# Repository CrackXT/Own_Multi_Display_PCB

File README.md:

# Own_Multi_Display_PCB

PCB files for Multi Display Board

# Description

This board serves as a development platform for finished devices with different display sizes.

- MiP 2,7" https://www.adafruit.com/product/4694
- TFT IPS 1,9" https://www.adafruit.com/product/5394
- TFT IPS 1,69" https://www.adafruit.com/product/5206
- TFT IPS 1,47" https://www.adafruit.com/product/5393

With a programmable status LED (RGB, SK6812-E) and an ambient light sensor (analogue, ALS-PT19) to regulate the brightness of TFT screens.

The screen, LED and ambient light sensor can be controlled via the existing Featherformat socket and the MCU used in it.

The board can be produced here (AISLER) with the files (.brd and .sch) or by any other PCB manufacturer. -> https://aisler.net/

# Serie

- .dev

# Layout

Top<br>

Bottom<br>

Routing/Dimensions(inch)<br>

Schematic<br>
Schematic as .pdf at the top of the page.

# License

Open hardware, use it, mod it, whatever you want, feel free...

# Thanks!

Own design and layout.

# Version - Build

v1.0 - 05.11.2022

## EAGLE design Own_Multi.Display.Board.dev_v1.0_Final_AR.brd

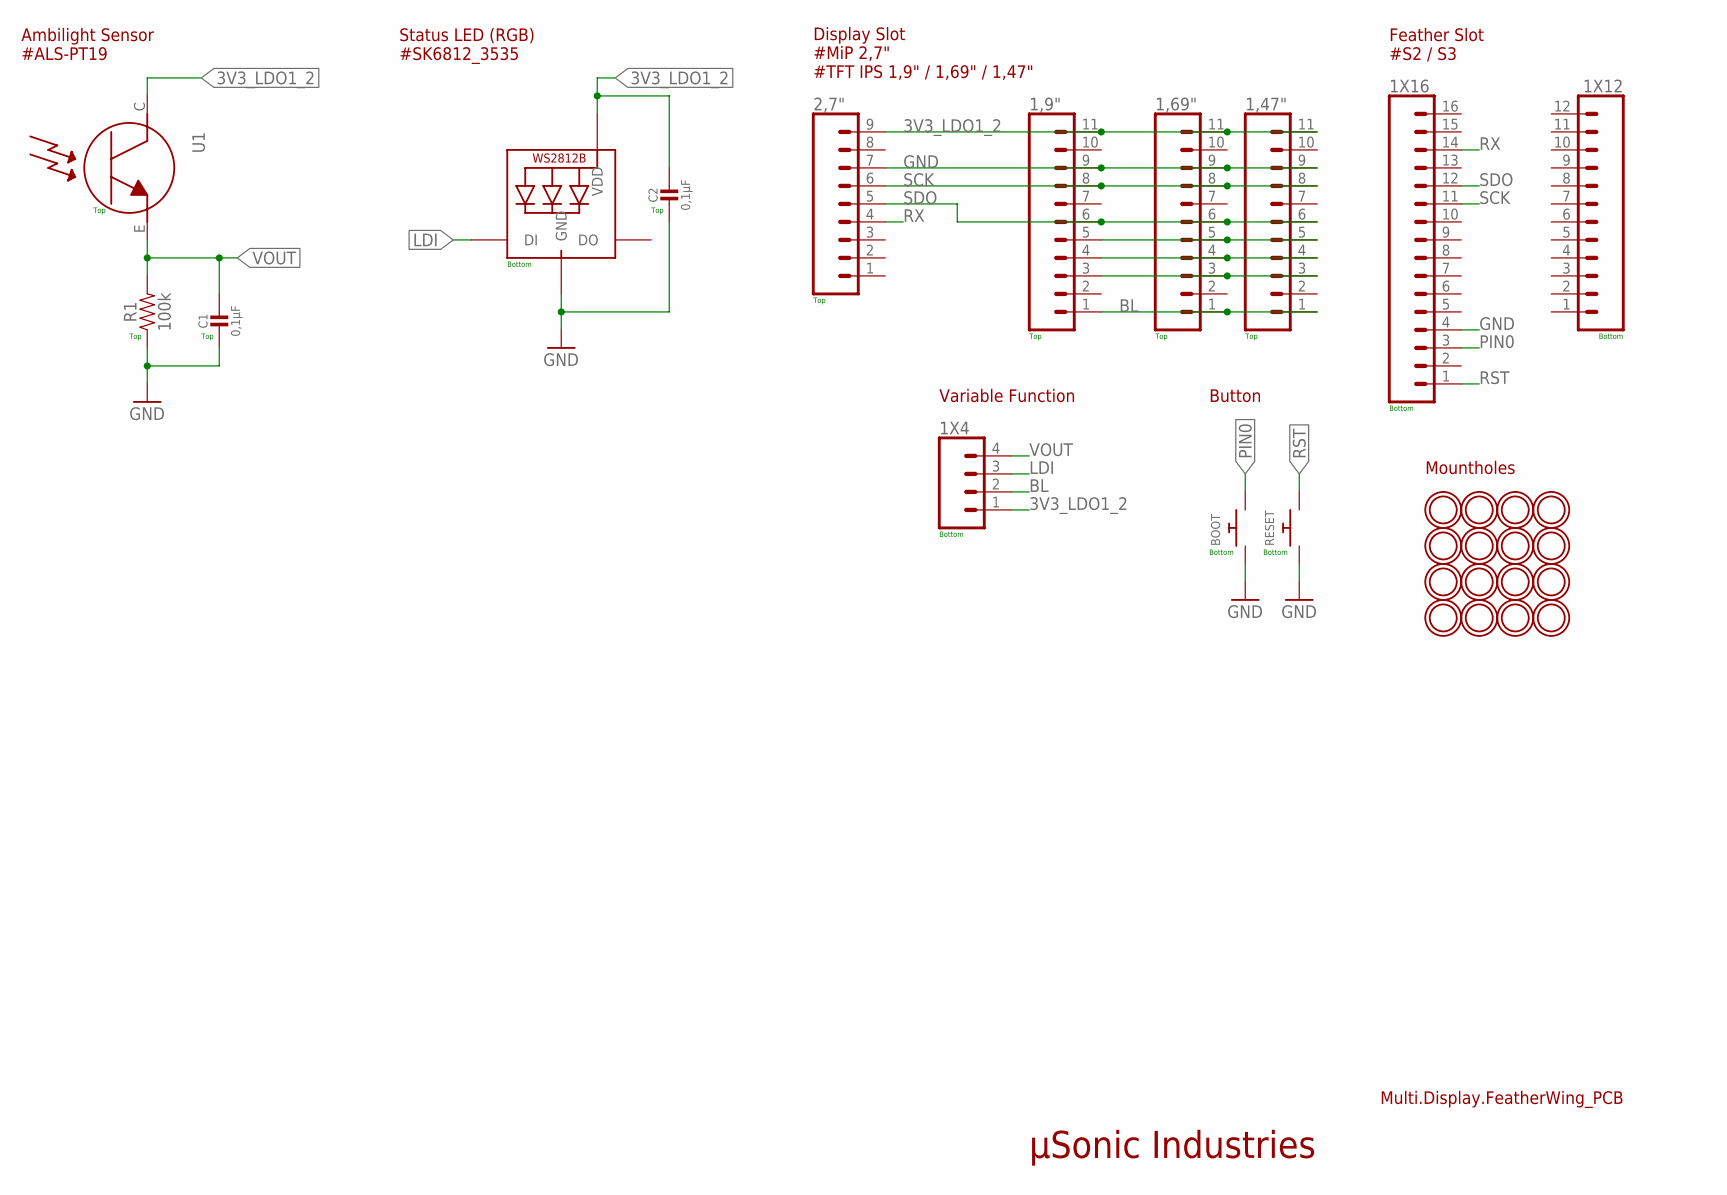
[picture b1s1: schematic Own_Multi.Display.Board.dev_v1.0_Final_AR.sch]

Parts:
1,9", 1,47", 1,69": CONN_111X11_NO_SILK; 1X11_NO_SILK
1X4: CONN_041X04_NO_SILK; 1X04_NO_SILK
1X12: CONN_12NO_SILK; 1X12_NO_SILK
1X16: CONN_161X16_NO_SILK; 1X16_NO_SILK
2,7": CONN_09NO_SILK; 1X09_NO_SILK
BOOT: SWITCH_PUSHBUTTONSF_OWN; OWN_TACT_PANA-EVQ
C1, C2: 0,1µF; MICROBUILDER_0805_10MGAP
LED1: MICROBUILDER_WS2812B_SK6812E; MICROBUILDER_NEO3535_REVERSE
R1: 100k; 0805
RESET: SWITCH_PUSHBUTTONSF_OWN; OWN_TACT_PANA-EVQ
U1: MICROBUILDER_LIGHT_ALS-PT19-315C; MICROBUILDER_ALS-PT19-315C
U$5, U$8, U$16, U$18, U$19, U$23, U$24, U$25, U$26, U$27, U$28, U$29, U$30, U$31, U$32, U$33: MOUNTINGHOLE2.5; MOUNTINGHOLE_2.5_PLATED

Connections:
3V3_LDO1_2: 1,9".11, 1,47".11, 1,69".11, 1X4.1, 2,7".9, C2.1, LED1.1-VDD (VDD), U1.C
BL: 1,9".1, 1,47".1, 1,69".1, 1X4.2
GND: 1,9".9, 1,47".9, 1,69".9, 1X16.4, 2,7".7, BOOT.P$1, C1.2, C2.2, LED1.3-GND (GND), R1.1, RESET.P$1
LDI: 1X4.3, LED1.4-DIN (DI)
unnamed: 1,9".5, 1,47".5, 1,69".5
unnamed: 1,9".4, 1,47".4, 1,69".4
unnamed: 1,9".3, 1,47".3, 1,69".3
PIN0: 1X16.3, BOOT.P$2
RST: 1X16.1, RESET.P$2
RX: 1X16.14, 2,7".4
SCK: 1,9".8, 1,47".8, 1,69".8, 1X16.11, 2,7".6
SDO: 1,9".6, 1,47".6, 1,69".6, 1X16.12, 2,7".5
VOUT: 1X4.4, C1.1, R1.2, U1.E

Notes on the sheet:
µSonic Industries
Multi.Display.FeatherWing_PCB
Ambilight Sensor #ALS-PT19
Mountholes
Top
Bottom
Status LED (RGB) #SK6812_3535
Display Slot #MiP 2,7" #TFT IPS 1,9" / 1,69" / 1,47"
Variable Function
Button
Feather Slot #S2 / S3

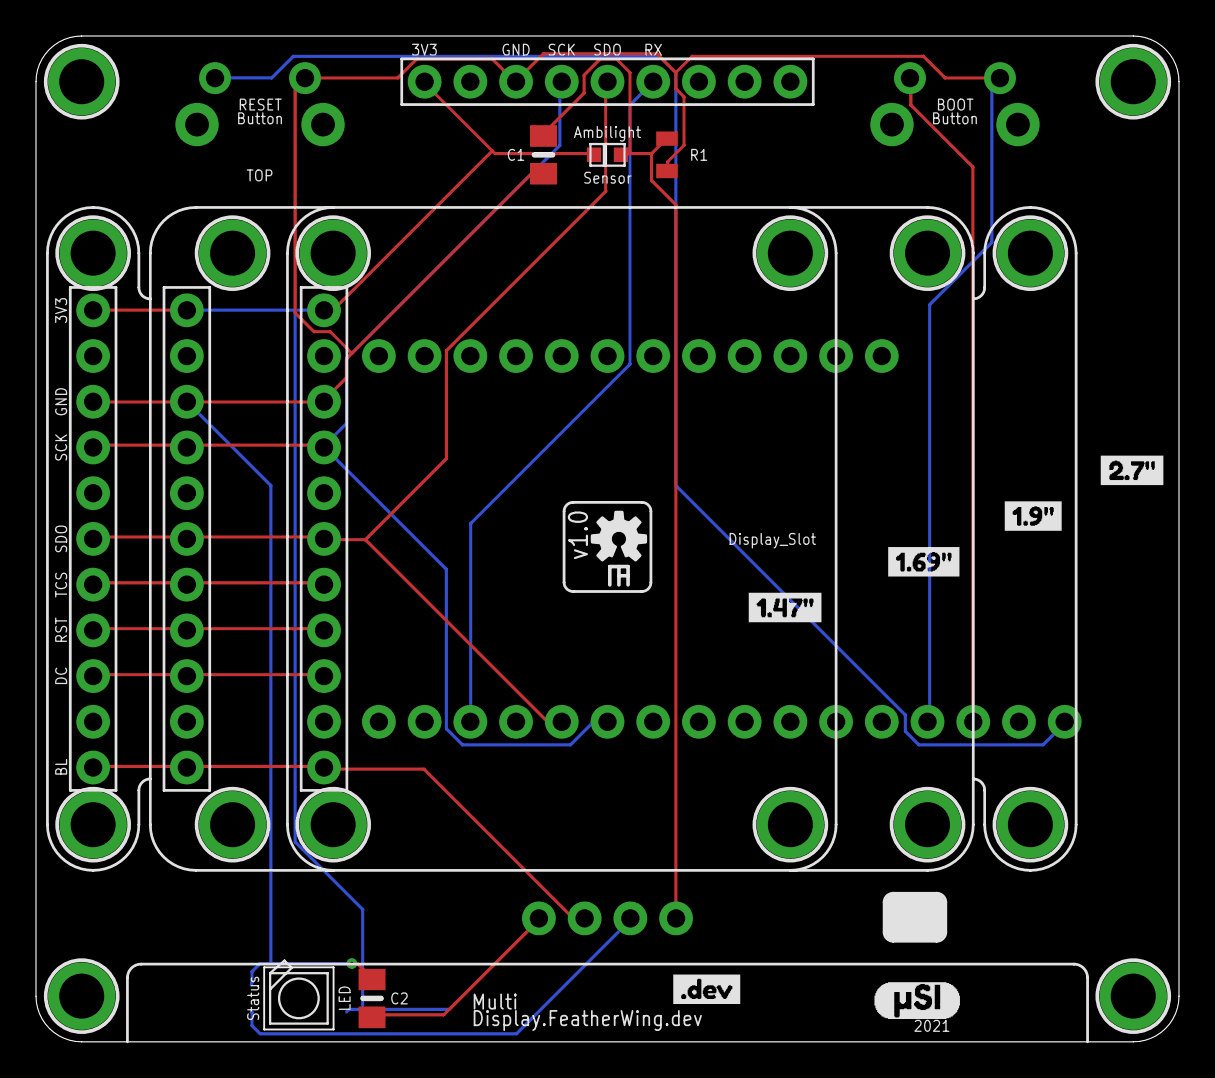
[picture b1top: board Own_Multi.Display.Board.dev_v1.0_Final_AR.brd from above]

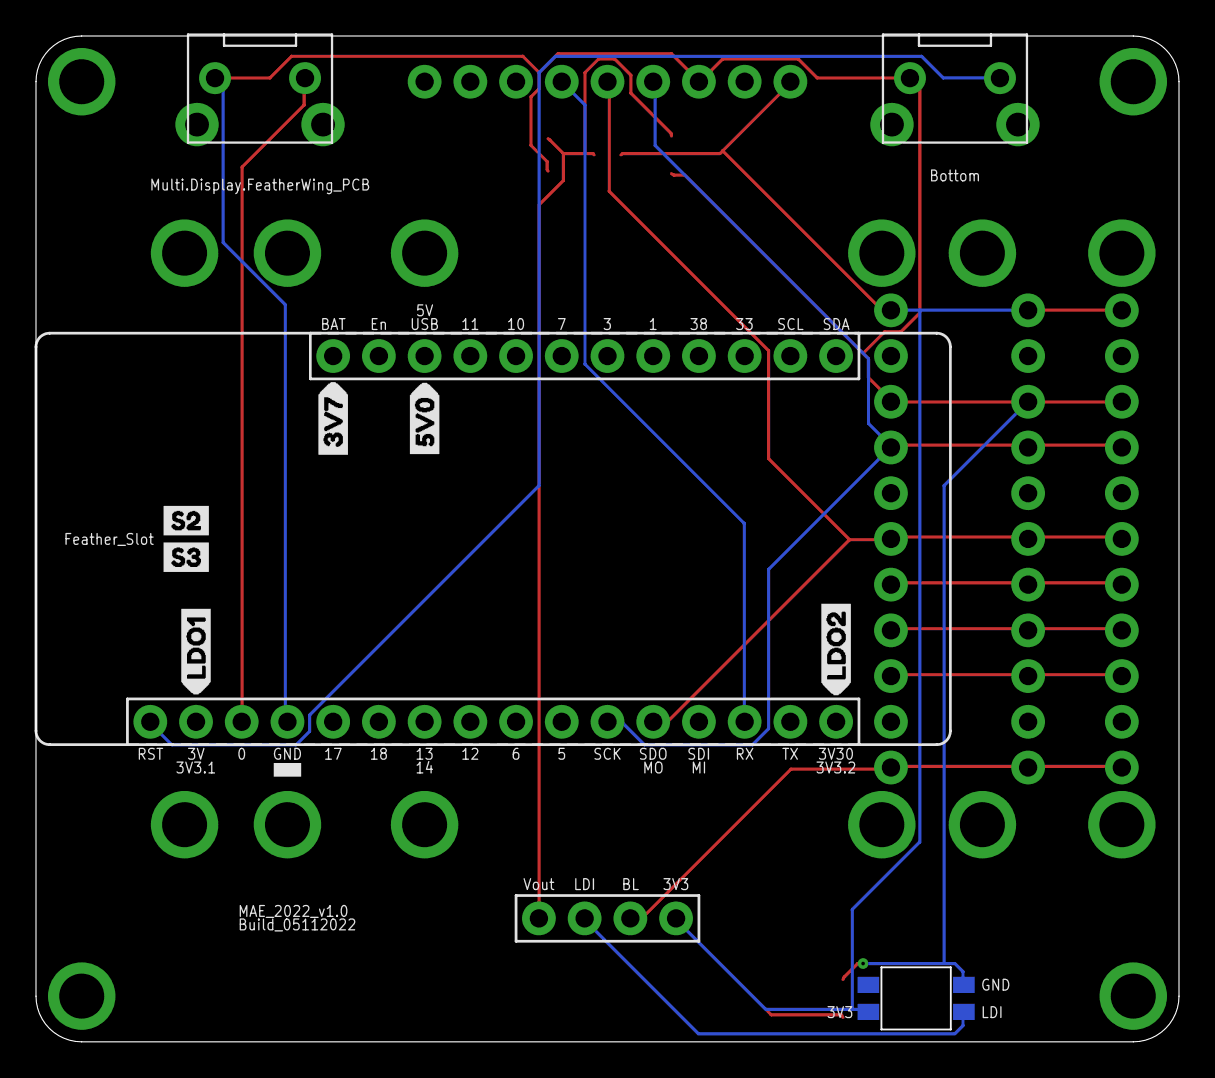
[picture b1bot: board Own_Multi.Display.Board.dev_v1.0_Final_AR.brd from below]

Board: 2 copper layers, 63.4 x 55.8 mm, 43 parts (8 on the bottom side), 13 nets.

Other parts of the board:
U$1: LDO15
U$4: OSHW-LOGO-S
U$6: #DEV15
U$7: LDO26
U$9: 3V72
U$10: 5V03
U$15: S212
U$17: S313
U$22: #SI0
U$34: 1#9#11
U$35: 1#69#10
U$36: 1#47#9
U$37: 2#7#12

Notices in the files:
parts and their libraries:
microbuilder: This work is placed in the public domain, and may be freely used for commercial and non-commercial work with the following conditions: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
SparkFun-Aesthetics: Licensing: Creative Commons ShareAlike 4.0 International - https://creativecommons.org/licenses/by-sa/4.0
